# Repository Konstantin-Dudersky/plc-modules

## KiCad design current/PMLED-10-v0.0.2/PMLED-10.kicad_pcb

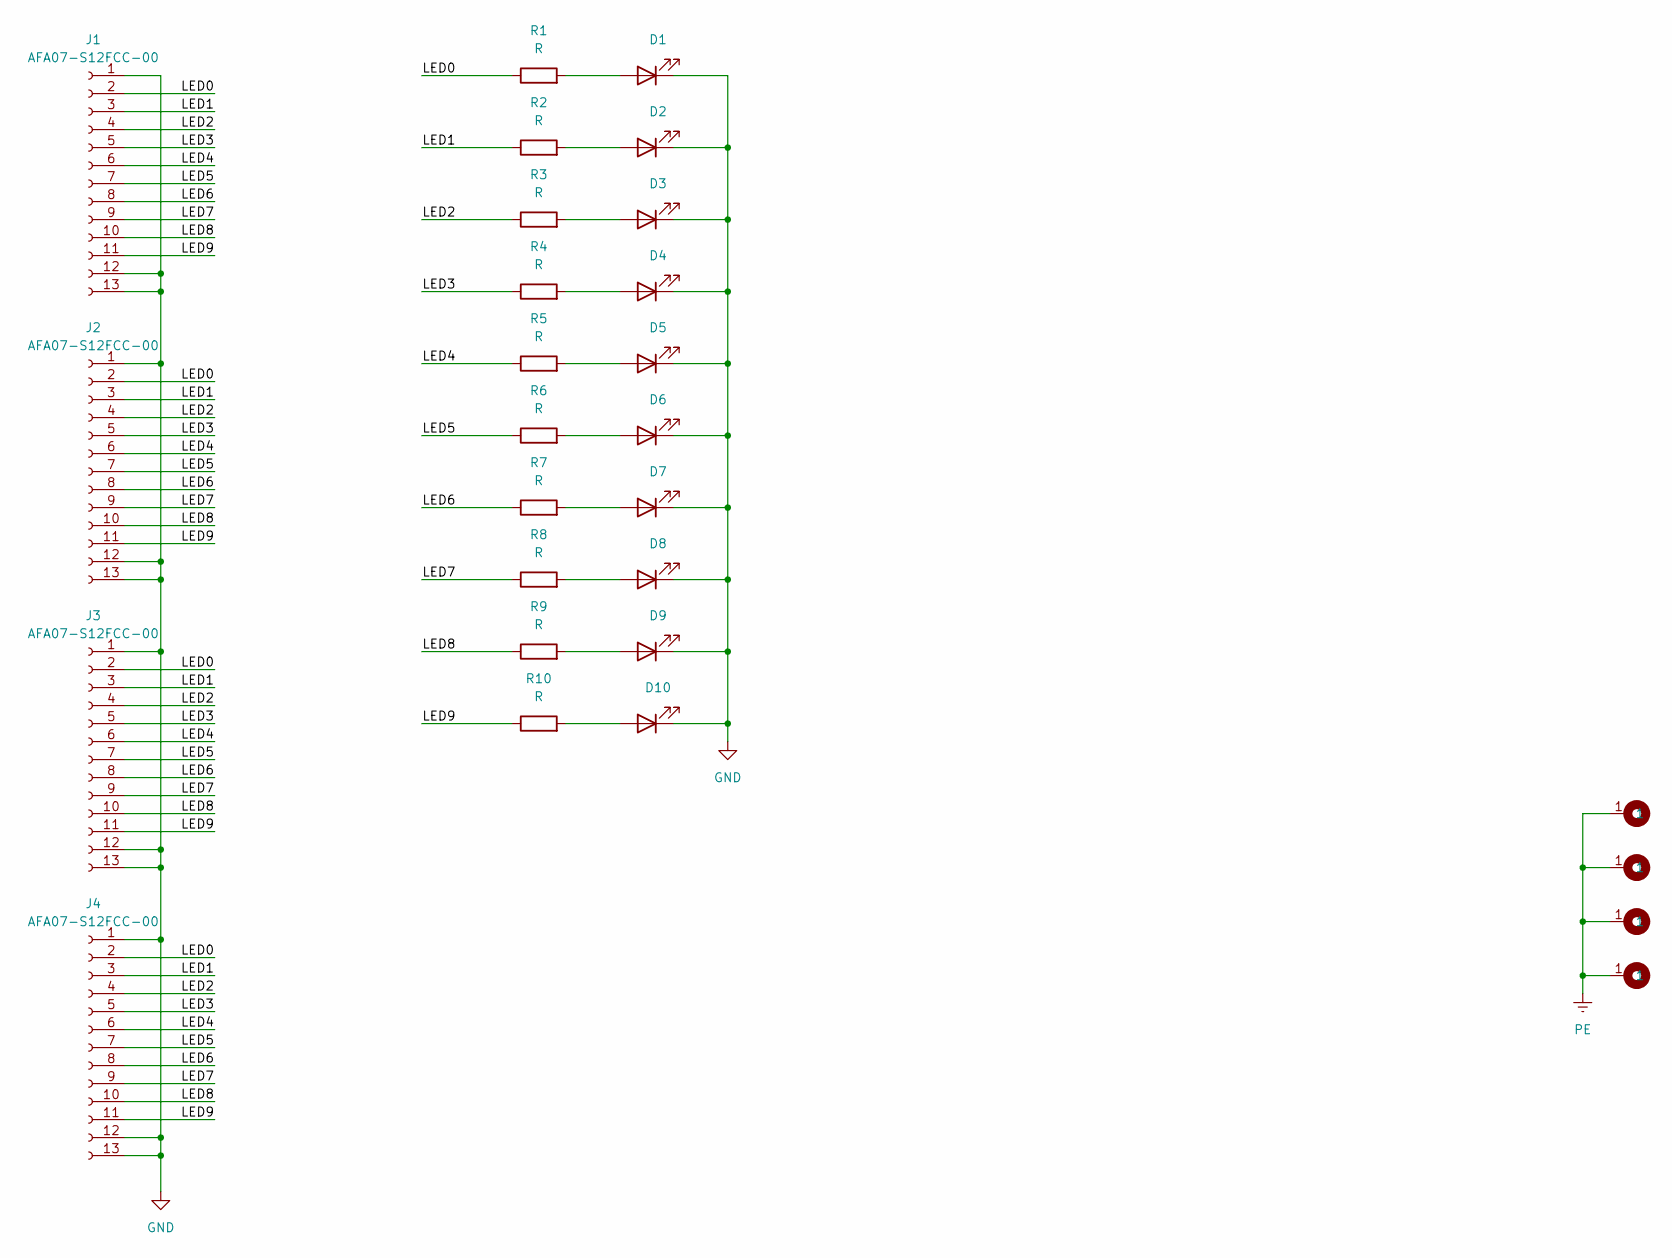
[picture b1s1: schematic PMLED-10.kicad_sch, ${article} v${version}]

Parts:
D1, D2, D3, D4, D5, D6, D7, D8, D9, D10: XL-1606SYGC; XL-1606; part_ipn XL-1606SYGC
H1, H2, H3, H5: M4; MountingHole_2.2mm_M2_Pad
J1, J2, J3, J4: AFA07-S12FCC-00; CONN10_AFA07-S12_JUS; part_ipn AFA07-S12FCC-00
R1, R2, R3, R4, R5, R6, R7, R8, R9, R10: R; R_0603_1608Metric

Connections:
/LED0: J1.2, J2.2, J3.2, J4.2, R1.1
/LED1: J1.3, J2.3, J3.3, J4.3, R2.1
/LED2: J1.4, J2.4, J3.4, J4.4, R3.1
/LED3: J1.5, J2.5, J3.5, J4.5, R4.1
/LED4: J1.6, J2.6, J3.6, J4.6, R5.1
/LED5: J1.7, J2.7, J3.7, J4.7, R6.1
/LED6: J1.8, J2.8, J3.8, J4.8, R7.1
/LED7: J1.9, J2.9, J3.9, J4.9, R8.1
/LED8: J1.10, J2.10, J3.10, J4.10, R9.1
/LED9: J1.11, J2.11, J3.11, J4.11, R10.1
GND: D1.1 (K), D2.1 (K), D3.1 (K), D4.1 (K), D5.1 (K), D6.1 (K), D7.1 (K), D8.1 (K), D9.1 (K), D10.1 (K), J1.1, J1.12 (Pin_11), J1.13 (Pin_11), J2.1, J2.12 (Pin_11), J2.13 (Pin_11), J3.1, J3.12 (Pin_11), J3.13 (Pin_11), J4.1, J4.12 (Pin_11), J4.13 (Pin_11)
unnamed: D1.2 (A), R1.2
unnamed: D2.2 (A), R2.2
unnamed: D3.2 (A), R3.2
unnamed: D4.2 (A), R4.2
unnamed: D5.2 (A), R5.2
unnamed: D6.2 (A), R6.2
unnamed: D7.2 (A), R7.2
unnamed: D8.2 (A), R8.2
unnamed: D9.2 (A), R9.2
unnamed: D10.2 (A), R10.2
PE: H1.1, H2.1, H3.1, H5.1

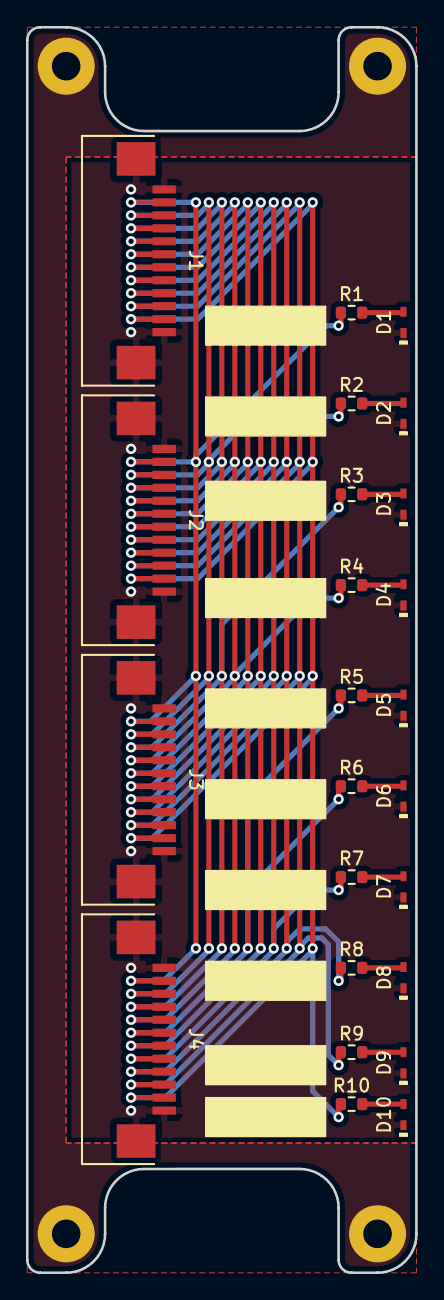
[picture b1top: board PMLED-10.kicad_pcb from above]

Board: 2 copper layers, 30.0 x 96.0 mm, 29 parts (1 on the bottom side), 22 nets.

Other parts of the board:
Logo_kicad: KiCad-Logo2_5mm_SilkScreen

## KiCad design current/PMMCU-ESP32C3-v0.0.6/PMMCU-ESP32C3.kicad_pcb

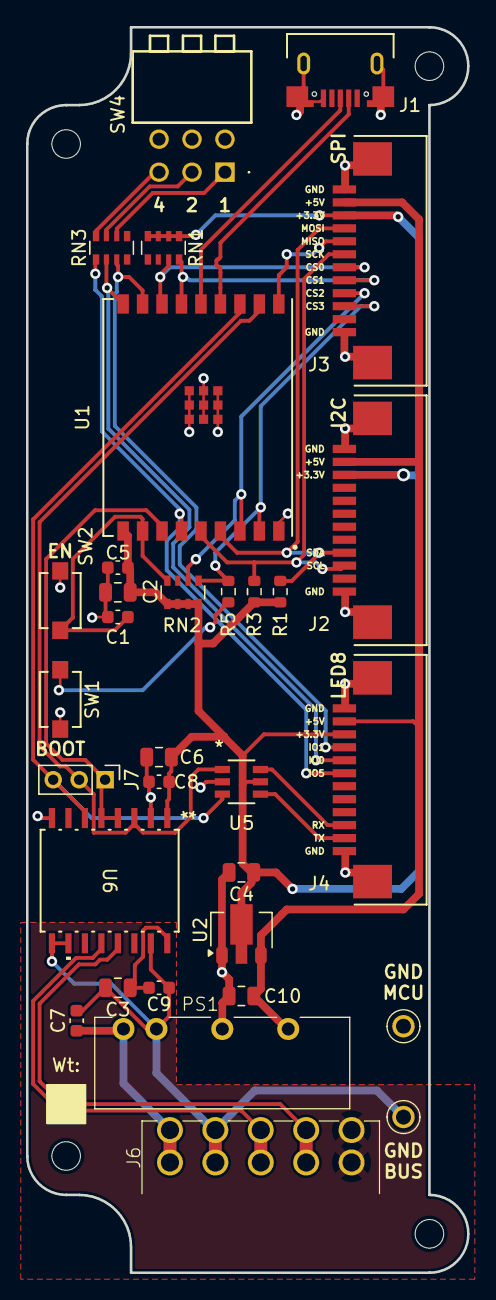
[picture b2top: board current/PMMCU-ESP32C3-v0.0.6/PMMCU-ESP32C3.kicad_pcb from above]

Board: 2 copper layers, 34.0 x 96.0 mm, 36 parts (0 on the bottom side), 31 nets.

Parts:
C1, C5, C7: 1uF; C_0603_1608Metric
C2, C3, C6, C10: 10uF; C_0805_2012Metric
C4: 22uF; C_0805_2012Metric
C8, C9: 100nF; C_0603_1608Metric
H1, H2, H3, H4: MountingHole_M2
J1: U254-051T-4BH83-S1S; CONN5_H83-S1S_XKB
J2, J3, J4: AFA07-S12FCC-00; CONN10_AFA07-S12_JUS
J6: 15EDGRHC-THR-3.5-10P
J7: PinHeader_01x03_P2.00_THT_straight; PinHeader_1x03_P2.00mm_Vertical
PS1: 24V/5V; B2405LS-1WR3
R1, R3: 3k3; R_0603_1608Metric
R5: 330R; R_0603_1608Metric
RN1, RN2, RN3: 10k; R_Array_Convex_4x0603
SW1, SW2: Button; SW_TS-1088_XNP-M
SW4: DIP 3 pos; DA03BLP
U1: ESP32-C3-WROOM-02U-N4; ESP32-C3-WROOM-02U_EXP
U2: CJA1117B-3.3; SOT-89-3
U3, U4: 5117
U5: SN74LVC2G14DBVR; DBV6-M
U6: CA-IS3098W; SOIC16-WBW_CLG

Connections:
+3.3V_BUS: C3.1, C9.1, U6.16 (VISO)
+3.3V_MCU: C2.1, C4.1, C5.1, C6.1, C8.1, J2.10, J3.10, J4.10, R1.1, R3.1, RN1.1 (R1.1), RN1.2 (R2.1), RN1.3 (R3.1), RN1.4 (R4.1), RN2.1 (R1.1), RN2.2 (R2.1), RN2.3 (R3.1), RN2.4 (R4.1), U1.1 (3V3), U2.2 (OUTPUT), U5.5 (VCC), U6.1 (VDD)
+5V_MCU: C10.1, J2.11, J3.11, J4.11, PS1.6 (+V), U2.3 (INPUT)
+24V_BUS: C7.1, J6.1, J6.6 (Pin_2), PS1.1 (Vin)
/A: J6.3, J6.8 (Pin_6), U6.12 (A)
/B: J6.4, J6.9 (Pin_8), U6.13 (B)
/CS0: J3.6, RN1.7 (R2.2), U1.16 (IO2)
/CS1: J3.5, RN1.8 (R1.2), U1.15 (IO3)
/CS2: J3.4, RN2.6 (R3.2), U1.7 (IO8)
/CS3: J3.3, R5.2, RN2.5 (R4.2), U1.8 (IO9)
/EN: C1.1, RN2.8 (R1.2), SW2.2, U1.2 (EN)
/LED0: J4.9, RN3.7 (R2.2), U1.17 (IO1)
/LED1: J4.8, RN3.6 (R3.2), U1.18 (IO0)
/LED2: J4.7, RN3.5 (R4.2), U1.4 (IO5)
/MISO: J3.8, U1.10 (IO10)
/MOSI: J2.4, J3.9, R1.2, U1.6 (IO7)
/SCK: J2.3, J3.7, R3.2, U1.5 (IO6)
/UART_RTS: J7.1, U1.3 (IO4), U6.4 (RE), U6.5 (DE)
/UART_RX: J7.2, U1.11 (RXD_(IO20)), U5.1 (1A), U6.3 (RO)
/UART_TX: J7.3, U1.12 (TXD_(IO21)), U5.3 (2A), U6.6 (DI)
/USB_D+: J1.3 (D+), U1.14 (IO19_(USB_D+))
/USB_D-: J1.2 (D-), U1.13 (IO18_(USB_D-))
GND_BUS: C3.2, C7.2, C9.2, J6.2 (Pin_3), J6.7 (Pin_4), PS1.2 (GND), U4.1, U6.9 (GNDB), U6.10 (SEL), U6.15 (GNDB)
GND_MCU: C1.2, C2.2, C4.2, C5.2, C6.2, C8.2, C10.2, J1.5 (GND), J2.1, J2.12 (Pin_11), J2.13 (Pin_11), J3.1, J3.12 (Pin_11), J3.13 (Pin_11), J4.1, J4.12 (Pin_11), J4.13 (Pin_11), PS1.4 (0V), SW1.1, SW2.1, SW4.4, SW4.5, SW4.6, U1.9 (GND), U1.EPAD, U2.1 (GND), U3.1, U5.2 (GND), U6.2 (GNDA), U6.8 (GNDA)
unnamed: J4.2, U5.4 (2Y)
unnamed: J4.3, U5.6 (1Y)
unnamed: R5.1, SW1.2
unnamed: RN3.2 (R2.1), SW4.1
unnamed: RN3.3 (R3.1), SW4.2
unnamed: RN3.4 (R4.1), SW4.3
PE: J6.5 (Pin_9), J6.10

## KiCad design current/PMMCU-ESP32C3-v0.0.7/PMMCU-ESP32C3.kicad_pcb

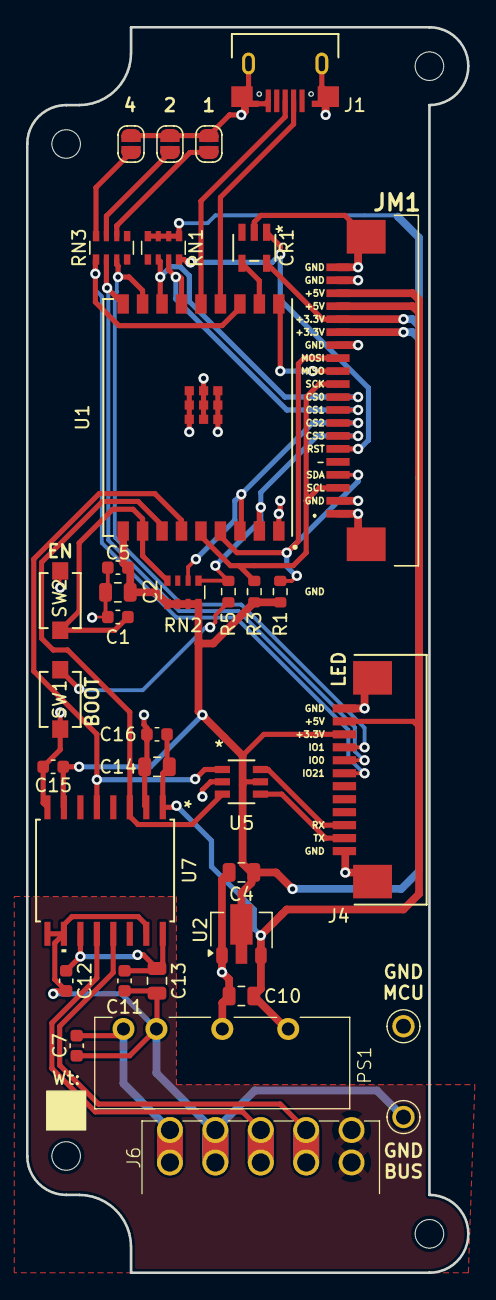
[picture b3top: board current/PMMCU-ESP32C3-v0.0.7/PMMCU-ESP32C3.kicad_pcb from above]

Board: 2 copper layers, 34.0 x 96.0 mm, 39 parts (0 on the bottom side), 32 nets.

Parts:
C1, C5, C7, C12, C15: 1uF; C_0603_1608Metric
C2, C10, C13, C14: 10uF; C_0805_2012Metric
C4: 22uF; C_0805_2012Metric
C11, C16: 100nF; C_0603_1608Metric
CR1: STWD100NYWY3F; SOT23-5L_STM
H1, H2, H3, H4: MountingHole_M2
J1: U254-051T-4BH83-S1S; CONN5_H83-S1S_XKB
J4: AFA07-S12FCC-00; CONN10_AFA07-S12_JUS
J6: 15EDGRHC-THR-3.5-10P
JM1: AFA07-S20FCC-00; AFA07S20FCA00
JP1, JP2, JP3: SolderJumper_2_Open; SolderJumper-2_P1.3mm_Open_RoundedPad1.0x1.5mm
PS1: 24V/5V; B2405LS-1WR3
R1, R3: 3k3; R_0603_1608Metric
R5: 330R; R_0603_1608Metric
RN1, RN2, RN3: 10k; R_Array_Convex_4x0603
SW1, SW2: Button; SW_TS-1088_XNP-M
U1: ESP32-C3-WROOM-02U-N4; ESP32-C3-WROOM-02U_EXP
U2: CJA1117B-3.3; SOT-89-3
U3, U4: 5117
U5: SN74LVC2G14DBVR; DBV6-M
U7: CA-IS3062VW; SOIC16-WBW_CLG-M

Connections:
+3.3V_MCU: C2.1, C4.1, C5.1, C15.1, CR1.5 (VCC), J4.10, JM1.15 (Pin_11), JM1.16 (Pin_11), R1.1, R3.1, RN1.1 (R1.1), RN1.2 (R2.1), RN1.3 (R3.1), RN1.4 (R4.1), RN2.1 (R1.1), RN2.2 (R2.1), RN2.3 (R3.1), RN2.4 (R4.1), U1.1 (3V3), U2.2 (OUTPUT), U5.5 (VCC), U7.7 (Vccl)
+5V_BUS: C11.1, C12.1, C13.1, U7.11 (Visoin), U7.16 (Viso)
+5V_MCU: C10.1, C14.1, C16.1, J4.11, JM1.17 (Pin_11), JM1.18 (Pin_11), PS1.6 (+V), U2.3 (INPUT), U7.1 (Vcc)
+24V_BUS: C7.1, J6.1, J6.6 (Pin_2), PS1.1 (Vin)
/CANH_BUS: J6.4, J6.9 (Pin_8), U7.13 (CANH)
/CANL_BUS: J6.3, J6.8 (Pin_6), U7.12 (CANL)
/CAN_RX: U1.4 (IO5), U5.1 (1A), U7.5 (RXD)
/CAN_TX: U1.3 (IO4), U5.3 (2A), U7.3 (TXD)
/CS0_MCU: JM1.10, RN1.6 (R3.2), U1.16 (IO2)
/CS1_MCU: JM1.9, RN1.7 (R2.2), U1.15 (IO3)
/CS2_MCU: JM1.8, RN2.6 (R3.2), U1.7 (IO8)
/CS3_MCU: JM1.7, R5.2, RN2.5 (R4.2), U1.8 (IO9)
/EN: C1.1, RN2.8 (R1.2), SW2.2, U1.2 (EN)
/LED0: J4.9, RN3.7 (R2.2), U1.17 (IO1)
/LED1: J4.8, RN3.6 (R3.2), U1.18 (IO0)
/LED2: J4.7, RN3.5 (R4.2), U1.12 (TXD_(IO21))
/MISO_MCU: JM1.12 (Pin_11), U1.10 (IO10)
/MOSI_SDA_MCU: JM1.4, JM1.13 (Pin_11), R1.2, U1.6 (IO7)
/RST: CR1.1 (*WDO), JM1.6, RN1.8 (R1.2)
/SCK_SCL_MCU: JM1.3, JM1.11, R3.2, U1.5 (IO6)
/USB_D+: J1.3 (D+), U1.14 (IO19_(USB_D+))
/USB_D-: J1.2 (D-), U1.13 (IO18_(USB_D-))
/WDT: CR1.4 (WDI), U1.11 (RXD_(IO20))
GND_BUS: C7.2, C11.2, C12.2, C13.2, J6.2 (Pin_3), J6.7 (Pin_4), PS1.2 (GND), U4.1, U7.9 (GND2), U7.10 (GND2), U7.15 (GND2)
GND_MCU: C1.2, C2.2, C4.2, C5.2, C10.2, C14.2, C15.2, C16.2, CR1.2 (GND), J1.5 (GND), J4.1, J4.12 (Pin_11), J4.13 (Pin_11), JM1.1, JM1.2, JM1.14 (Pin_11), JM1.19 (Pin_11), JM1.20 (Pin_11), JM1.MP1 (Pin_11), JM1.MP2 (Pin_11), JP1.2 (B), JP2.2 (B), JP3.2 (B), PS1.4 (0V), SW1.1, SW2.1, U1.9 (GND), U1.EPAD, U2.1 (GND), U3.1, U5.2 (GND), U7.2 (GND1), U7.8 (GND1)
unnamed: J4.2, U5.4 (2Y)
unnamed: J4.3, U5.6 (1Y)
unnamed: JP1.1 (A), RN3.4 (R4.1)
unnamed: JP2.1 (A), RN3.3 (R3.1)
unnamed: JP3.1 (A), RN3.2 (R2.1)
unnamed: R5.1, SW1.2
PE: J6.5 (Pin_9), J6.10

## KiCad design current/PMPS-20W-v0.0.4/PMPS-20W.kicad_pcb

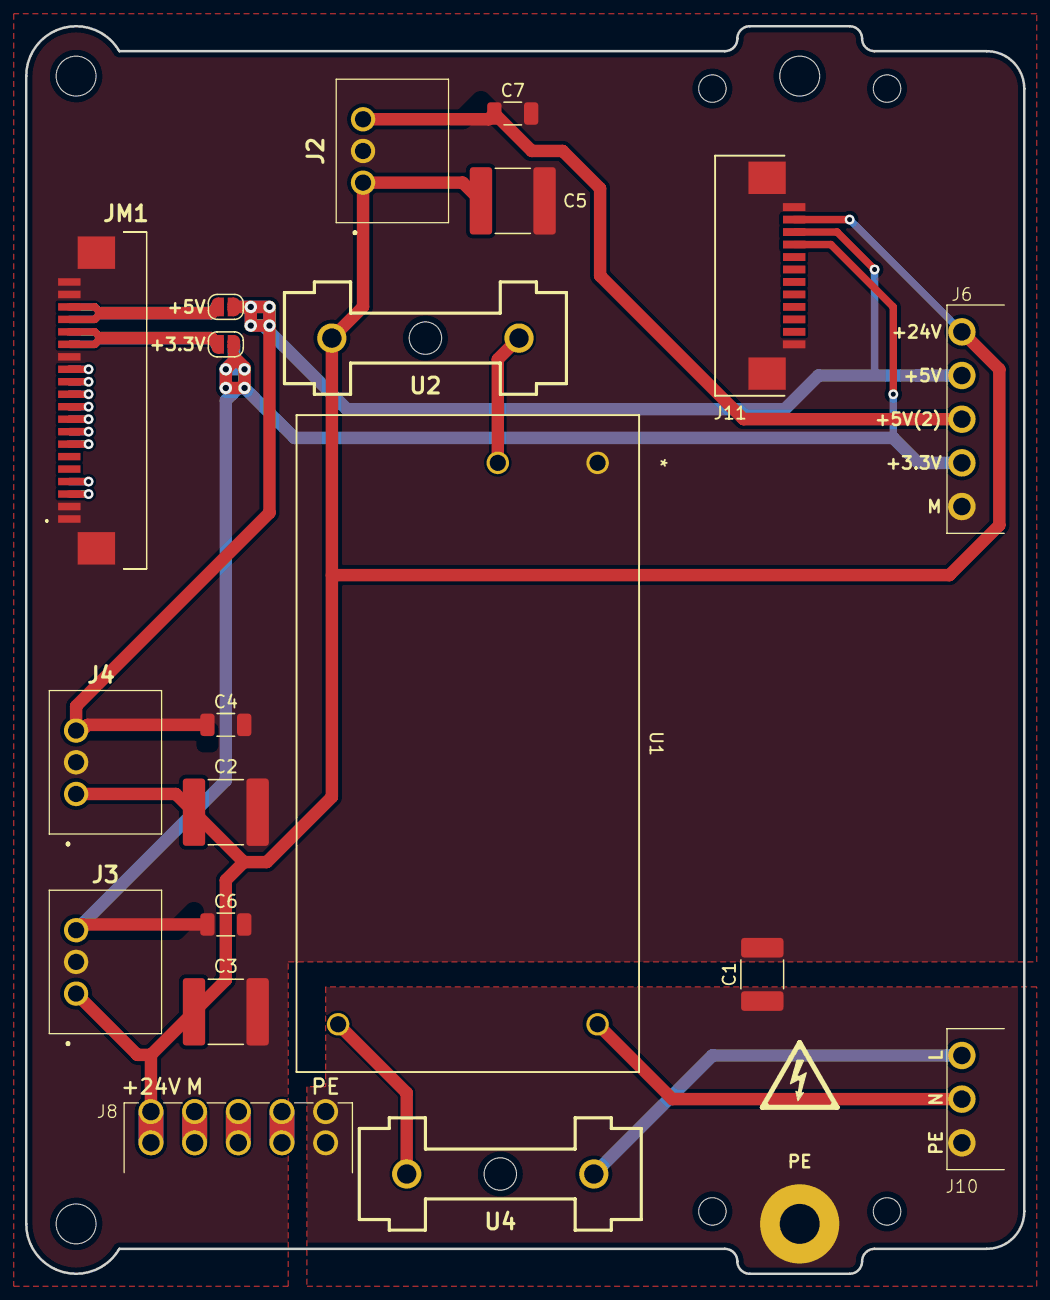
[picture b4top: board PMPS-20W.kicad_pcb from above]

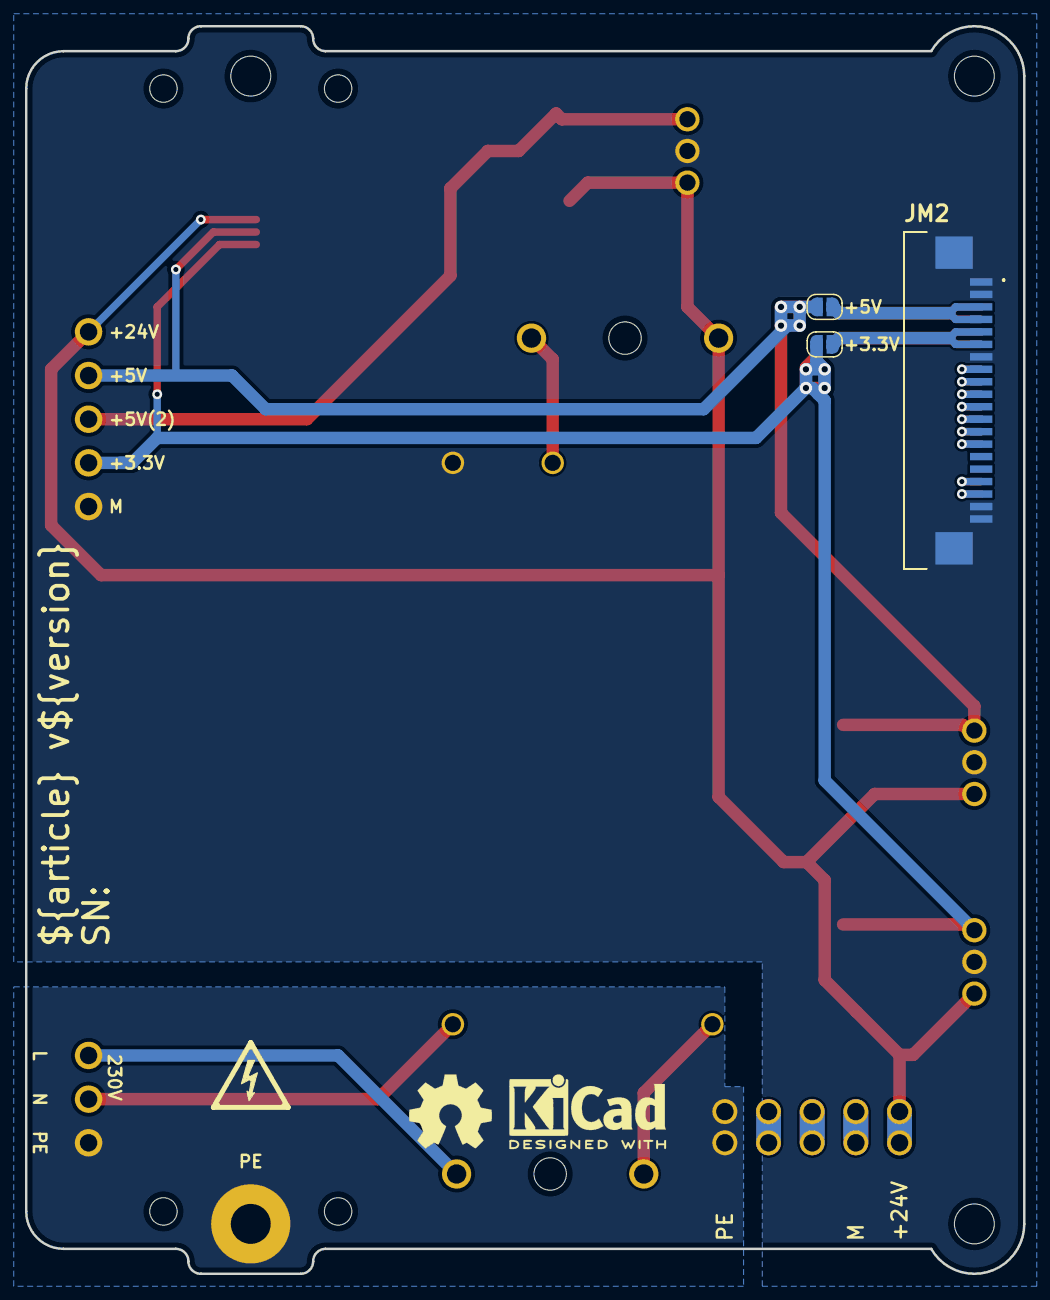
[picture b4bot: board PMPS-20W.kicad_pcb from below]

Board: 2 copper layers, 80.0 x 100.0 mm, 30 parts (5 on the bottom side), 29 nets.

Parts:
C1: 4.7nF 2kV; C_1812_4532Metric_Pad1.57x3.40mm_HandSolder
C2, C3, C5: 22uF; C_2220_5750Metric
C4, C6, C7: 22uF; C_1206_3216Metric
H1, H2, H3: MountingHole_M3
J2, J4: K7805-2000R3
J3: K7803-2000R3; K7805-2000R3
J6: 15EDGRC-3.5-05P
J8: 15EDGRHC-THR-3.5-10P
J10: 15EDGRC-3.5-03P
J11: AFA07-S12FCC-00; CONN10_AFA07-S12_JUS
JM1, JM2: AFA07-S20FCC-00; AFA07S20FCA00
JP1, JP2, JP3, JP4: SolderJumper_2_Open; SolderJumper-2_P1.3mm_Open_RoundedPad1.0x1.5mm
PE1: PE
SP1: PM_LED-xx-v0.0.1
U1: IRM-20-24; IRM-20-24_MWU
U2, U4: 64900001039; 649-Series-Holder
kicad_logo: KiCad-Logo2_5mm_SilkScreen
oshw_logo: OSHW-Symbol_6.7x6mm_SilkScreen

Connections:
230V: J10.3, U4.1
+3V3: C6.1, J3.3 (+VO), J6.2, J11.4, JP3.2 (B), JP4.1 (A)
+3V3-IB-back: JM2.5, JM2.6, JP4.2 (B)
+3V3-IB-front: JM1.15 (Pin_11), JM1.16 (Pin_11), JP3.1 (A)
+5V: C4.1, J4.3 (+VO), J6.4, J11.3, JP1.2 (B), JP2.1 (A)
+5V(2): C7.1, J2.3 (+VO), J6.3
+5V-IB-back: JM2.3, JM2.4, JP2.2 (B)
+5V-IB-front: JM1.17 (Pin_11), JM1.18 (Pin_11), JP1.1 (A)
+24V: C2.1, C3.1, C5.1, J2.1 (VIN), J3.1 (VIN), J4.1 (VIN), J6.5, J11.2, U2.2
+24V_EB: J8.1, J8.6 (Pin_2)
/CANH_EB: J8.4, J8.9 (Pin_8)
/CANL_EB: J8.3, J8.8 (Pin_6)
/CS0_IB: JM1.10, JM2.11
/CS1_IB: JM1.9, JM2.12 (Pin_11)
/CS2_IB: JM1.8, JM2.13 (Pin_11)
/CS3_IB: JM1.7, JM2.14 (Pin_11)
/MISO_IB: JM1.12 (Pin_11), JM2.9
/MOSI_IB: JM1.13 (Pin_11), JM2.8
/RST_IB: JM1.6, JM2.15 (Pin_11)
/SCK_IB: JM1.11, JM2.10
/SCL_IB: JM1.3, JM2.18 (Pin_11)
/SDA_IB: JM1.4, JM2.17 (Pin_11)
GND_EB: J8.2 (Pin_3), J8.7 (Pin_4)
GND_MCU: C1.2, C2.2, C3.2, C4.2, C5.2, C6.2, C7.2, J2.2 (GND), J3.2 (GND), J4.2 (GND), J6.1, J11.1, J11.12 (Pin_11), J11.13 (Pin_11), JM1.1, JM1.2, JM1.14 (Pin_11), JM1.19 (Pin_11), JM1.20 (Pin_11), JM1.MP1 (Pin_11), JM1.MP2 (Pin_11), JM2.1, JM2.2, JM2.7, JM2.19 (Pin_11), JM2.20 (Pin_11), JM2.MP1 (Pin_11), JM2.MP2 (Pin_11), U1.1 (V-)
N: J10.2, U1.4 (AC/N)
unnamed: JM1.5, JM2.16 (Pin_11)
unnamed: U1.3 (AC/L), U4.2
unnamed: U1.2 (V+), U2.1
PE: C1.1, J8.5 (Pin_9), J8.10, J10.1, PE1.1

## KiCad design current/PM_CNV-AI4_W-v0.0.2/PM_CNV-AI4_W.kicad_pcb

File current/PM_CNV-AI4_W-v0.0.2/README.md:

## v0.0.2

- Вместо двух AD7190 - один AD7193

Подключить GND к AINCOM

Подключить референс только к Refin1

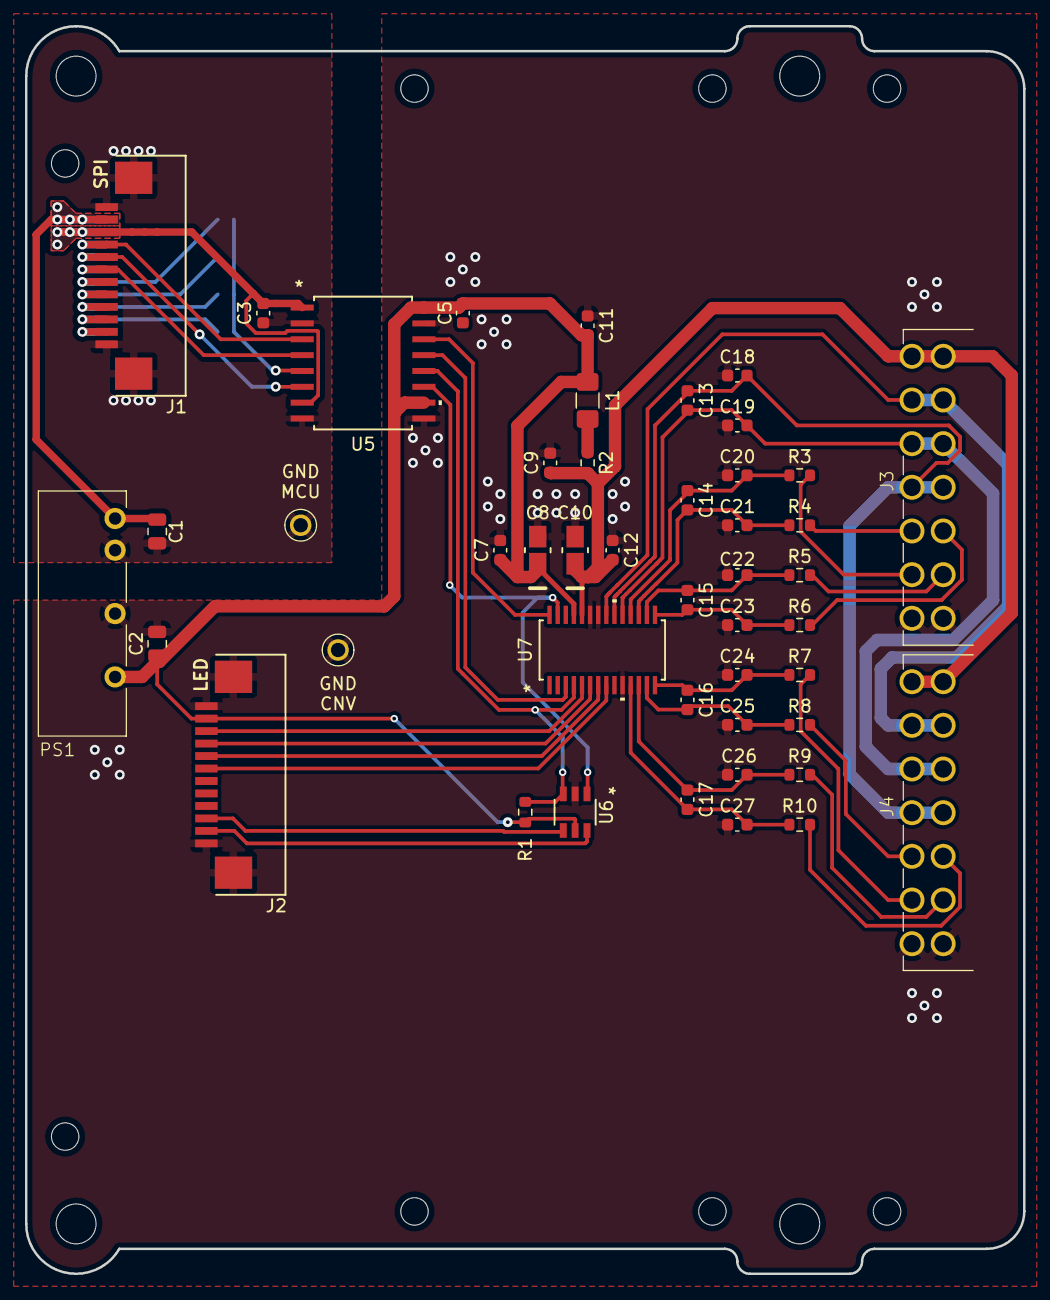
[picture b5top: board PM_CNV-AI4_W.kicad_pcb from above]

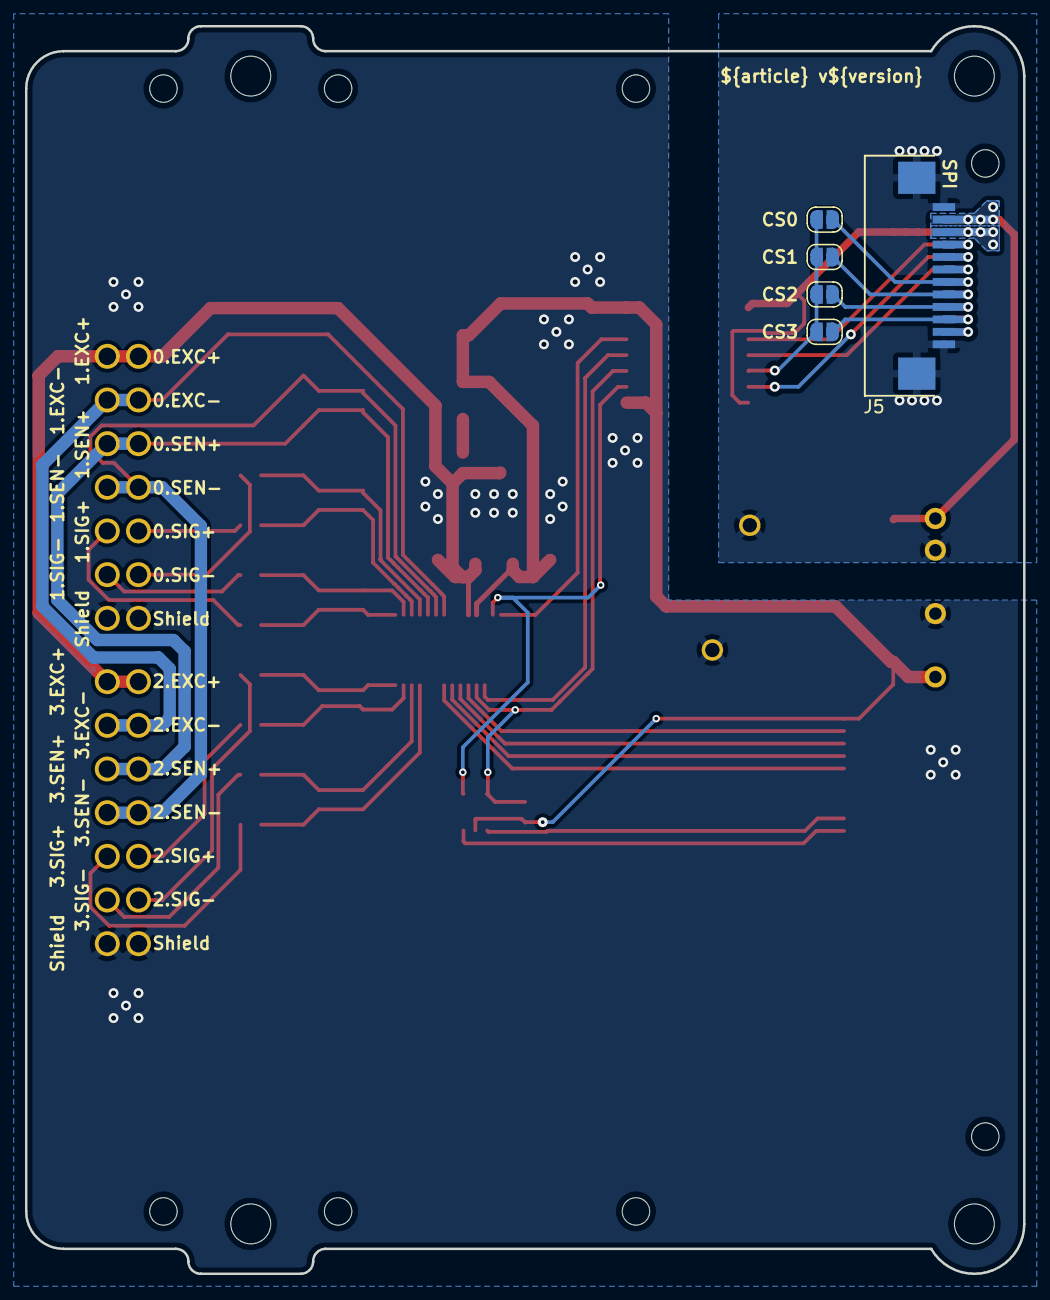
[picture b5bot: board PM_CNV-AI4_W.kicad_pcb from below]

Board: 2 copper layers, 80.0 x 100.0 mm, 57 parts (5 on the bottom side), 45 nets.

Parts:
C1: 4.7uF; C_0805_2012Metric
C2: 10uF; C_0805_2012Metric
C3, C5, C7, C9, C11, C12: 100nF; C_0603_1608Metric
C8, C10: 10 uF; TAJA_AVX-M
C13: 1uF; C_0603_1608Metric
C14, C15, C16, C17, C18, C19: 10nF; C_0603_1608Metric
C20, C21, C22, C23, C24, C25, C26, C27: 1nF; C_0603_1608Metric
H1, H2, H3, H4: MountingHole_M3
J1, J2, J5: AFA07-S12FCC-00; CONN10_AFA07-S12_JUS
J3, J4: 15EDGRHC-THR-3.5-14P
JP1, JP2, JP3, JP4: SolderJumper_2_Open; SolderJumper-2_P1.3mm_Open_RoundedPad1.0x1.5mm
L1: 1kΩ@100MHz; L_1206_3216Metric_Pad1.42x1.75mm_HandSolder
PS1: 5V/5V; B2405LS-1WR3
R1: 10k; R_0603_1608Metric
R2: 1R5; R_0603_1608Metric
R3, R4, R5, R6, R7, R8, R9, R10: 100R; R_0603_1608Metric
SP1: PM_LED-xx-v0.0.1
U1: PM-ESP32C3_v0.0.5
U2, U3: 5117
U5: CA-IS3741HW; SOIC16-WBW_CLG-M
U6: SN74LVC2G14DBVR; DBV6-M
U7: AD7193BRUZ; RU_28_ADI

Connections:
+3.3V_MCU: C3.1, J1.10, J5.3, U5.1 (VDD), U5.7 (ENA)
+5V_CNV: C2.1, C5.2, C7.1, C8.1, C11.1, J2.11, L1.2, PS1.6 (+V), R1.1, U5.10 (ENB), U5.16 (VISO), U6.5 (VCC), U7.25 (DVDD)
+5V_CNV_FLT: C9.1, C10.1, C12.1, J3.7 (Pin_9), J3.14 (Pin_10), J4.7 (Pin_9), J4.14 (Pin_10), R2.2, U7.24 (AVDD)
+5V_MCU: C1.1, J1.11, J5.2, PS1.1 (Vin)
/0.SIG+: J3.3, R4.2
/0.SIG-: J3.2 (Pin_3), R3.2
/1.SIG+: J3.10 (Pin_6), R6.2
/1.SIG-: J3.9 (Pin_4), R5.2
/2.SIG+: J4.3, R8.2
/2.SIG-: J4.2 (Pin_3), R7.2
/3.SIG+: J4.10 (Pin_6), R10.2
/3.SIG-: J4.9 (Pin_4), R9.2
/AIN1: C17.1, C27.1, R10.1, U7.11 (AIN1)
/AIN2: C17.2, C26.1, R9.1, U7.12 (AIN2)
/AIN3: C16.1, C25.1, R8.1, U7.13 (AIN3)
/AIN4: C16.2, C24.1, R7.1, U7.14 (AIN4)
/AIN5: C15.1, C23.1, R6.1, U7.15 (AIN5)
/AIN6: C15.2, C22.1, R5.1, U7.16 (AIN6)
/AIN7: C14.1, C21.1, R4.1, U7.17 (AIN7)
/AIN8: C14.2, C20.1, R3.1, U7.18 (AIN8)
/CS0_MCU: J1.6, J5.7, JP1.1 (A)
/CS1_MCU: J1.5, J5.8, JP2.1 (A)
/CS2_MCU: J1.4, J5.9, JP3.1 (A)
/CS3_MCU: J1.3, J5.10, JP4.1 (A)
/CS_CNV: R1.2, U5.12 (VO3), U6.3 (2A), U7.4 (CS)
/CS_LED: J2.3, U6.4 (2Y)
/CS_MCU: JP1.2 (B), JP2.2 (B), JP3.2 (B), JP4.2 (B), U5.5 (VI3)
/EXC-: J3.6 (Pin_9), J3.13 (Pin_10), J4.6 (Pin_9), J4.13 (Pin_10), U7.21 (BPDSW)
/INT_MCU: J1.2, J5.11
/MISO_CNV: U5.11 (VI4), U6.1 (1A), U7.27 (MISO)
/MISO_LED: J2.2, U6.6 (1Y)
/MISO_MCU: J1.8, J5.5, U5.6 (VO4)
/MOSI_CNV: U5.14 (VO1), U7.28 (MOSI)
/MOSI_MCU: J1.9, J5.4, U5.3 (VI1)
/P0: J2.7, U7.8 (P0)
/P1: J2.8, U7.7 (P1)
/P2: J2.9, U7.6 (P2)
/P3: J2.10, U7.5 (P3)
/SCK_CNV: U5.13 (VO2), U7.3 (SCK)
/SCK_MCU: J1.7, J5.6, U5.4 (VI2)
/SENSE+: C13.1, C19.1, J3.5 (Pin_9), J3.12 (Pin_10), J4.5 (Pin_9), J4.12 (Pin_10), U7.19 (REFIN1(+))
/SENSE-: C13.2, C18.1, J3.4, J3.11 (Pin_8), J4.4, J4.11 (Pin_8), U7.20 (REFIN1(-))
GND_CNV: C2.2, C7.2, C8.2, C9.2, C10.2, C11.2, C12.2, C18.2, C19.2, C20.2, C21.2, C22.2, C23.2, C24.2, C25.2, C26.2, C27.2, J2.1, J2.12 (Pin_11), J2.13 (Pin_11), J3.1, J3.8 (Pin_2), J4.1, J4.8 (Pin_2), PS1.4 (0V), U3.1, U5.9 (GNDB), U5.15 (GNDB), U6.2 (GND), U7.10 (AINCOM), U7.22 (AGND), U7.23 (DGND)
GND_MCU: C1.2, C3.2, J1.1, J1.12 (Pin_11), J1.13 (Pin_11), J5.1, J5.12 (Pin_11), J5.13 (Pin_11), PS1.2 (GND), U2.1, U5.2 (GNDA), U5.8 (GNDA)
unnamed: L1.1, R2.1

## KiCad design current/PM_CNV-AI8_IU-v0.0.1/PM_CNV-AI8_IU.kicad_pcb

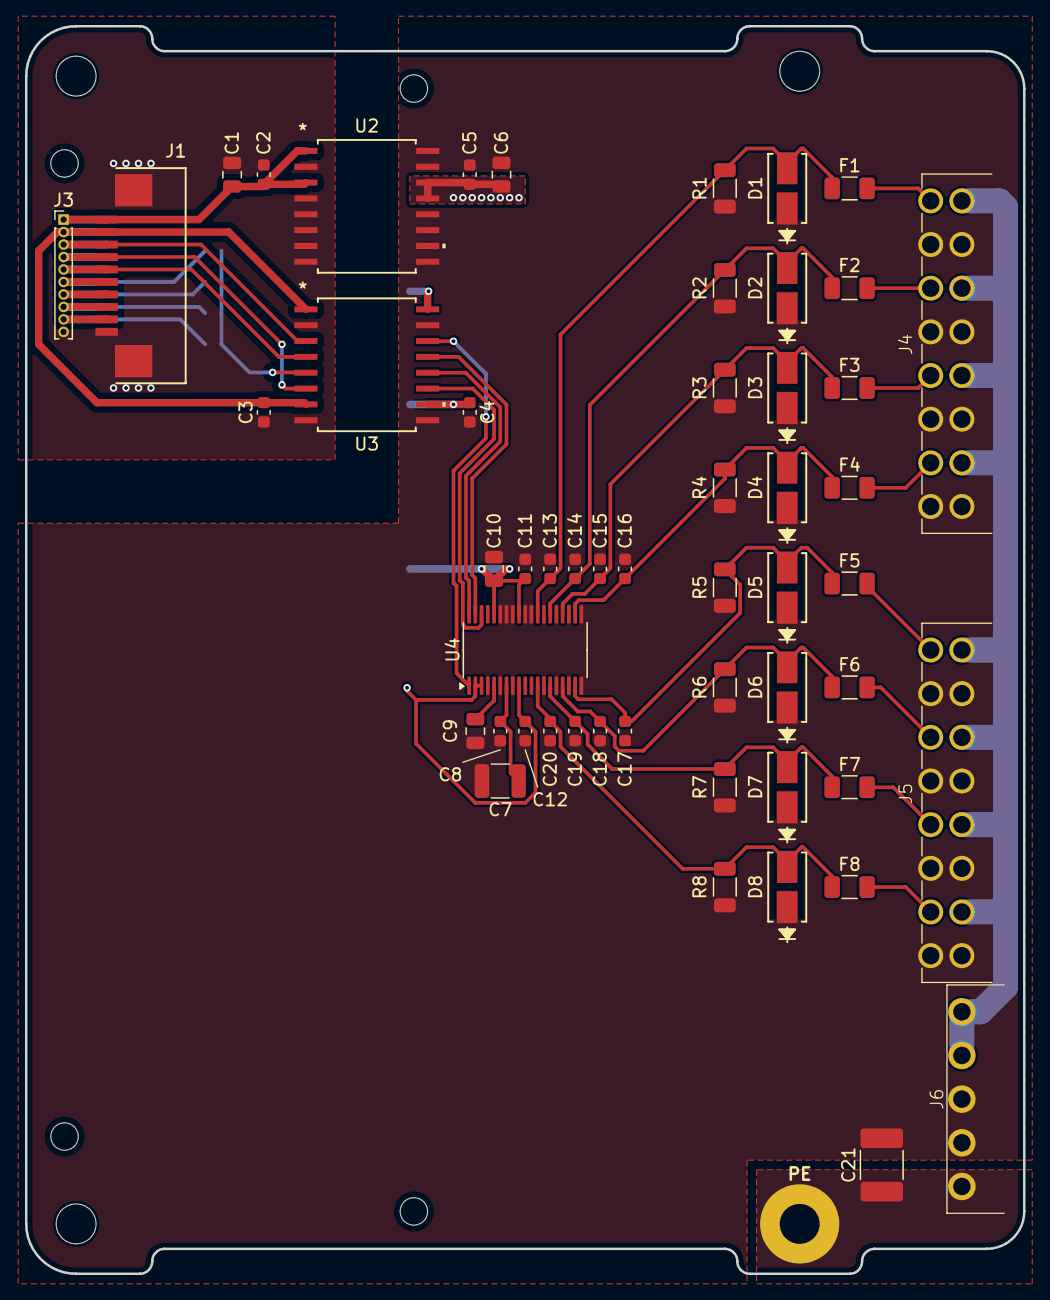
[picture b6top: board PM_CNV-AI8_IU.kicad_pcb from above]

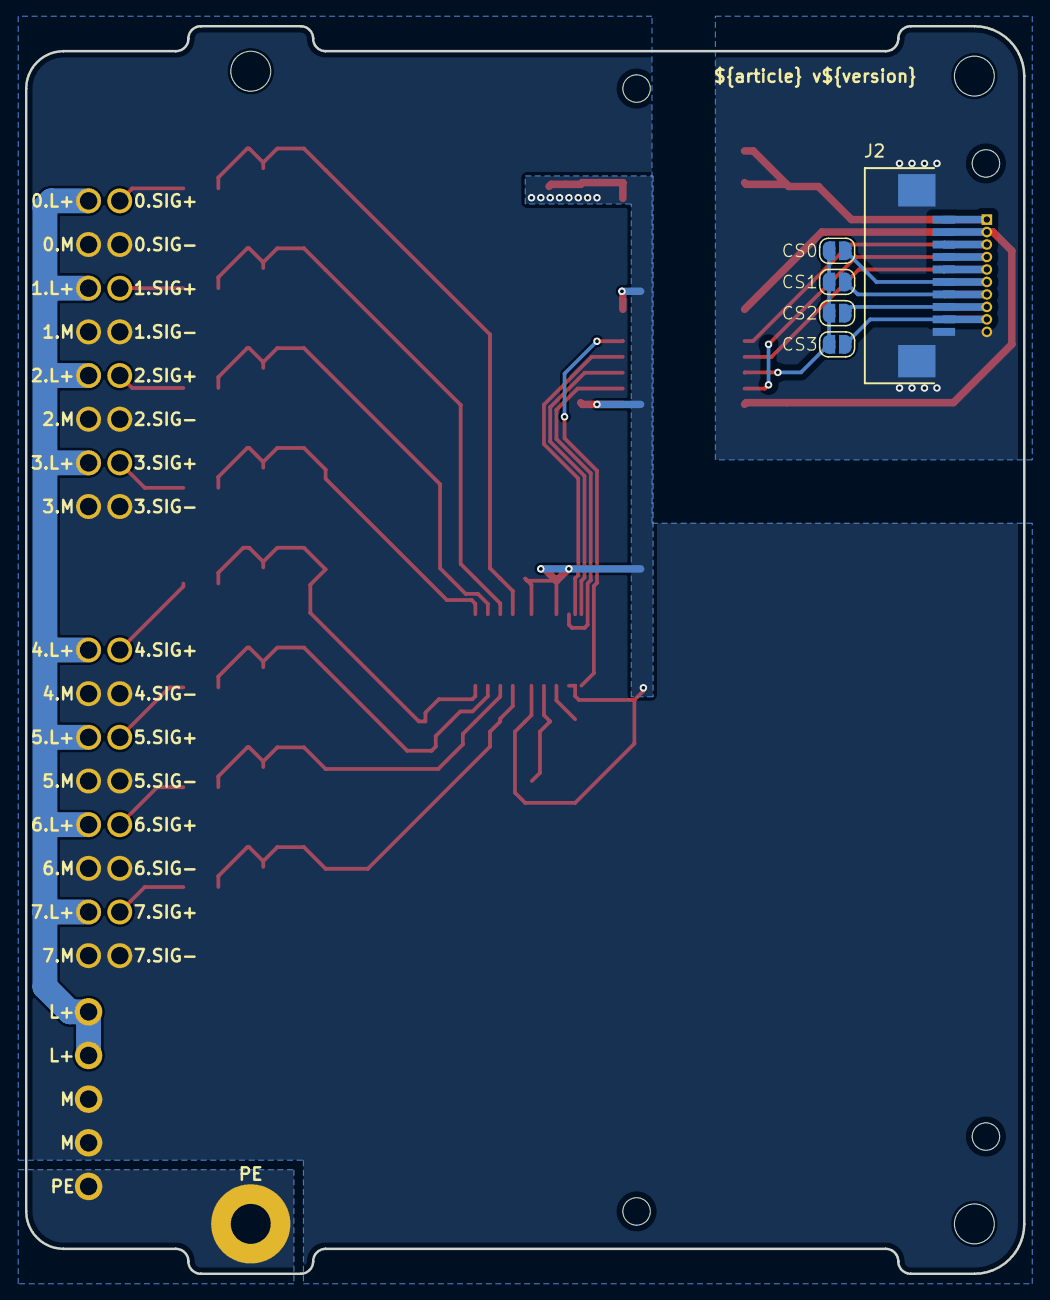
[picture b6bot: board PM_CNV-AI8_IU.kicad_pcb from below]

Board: 2 copper layers, 80.0 x 100.0 mm, 63 parts (5 on the bottom side), 37 nets.

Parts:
C1, C6, C9, C10: 10uF; C_0805_2012Metric
C2, C3, C4, C5: 100nF; C_0603_1608Metric
C7: 22uF; C_1210_3225Metric
C8, C11, C12: 1uF; C_0603_1608Metric
C13, C14, C15, C16, C17, C18, C19, C20: 10nF; C_0603_1608Metric
C21: 4.7nF 2kV; C_1812_4532Metric_Pad1.57x3.40mm_HandSolder
D1, D2, D3, D4, D5, D6, D7, D8: SMAJ33CA; SMASeries_LTF-M
D9: PE
F1, F2, F3, F4, F5, F6, F7, F8: nSMD005; Fuse_1206_3216Metric
H1, H2, H3: MountingHole; MountingHole_3.2mm_M3
J1, J2: AFA07-S10FCC-00; CONN10_AFA07-S10_JUS
J3: PinHeader_01x10_P1.00_THT_straight; PinHeader_1x10_P1.00mm_Vertical
J4, J5: 15EDGRHC-THR-3.5-16P
J6: 15EDGRC-3.5-05P
JP1, JP2, JP3, JP4: SolderJumper_2_Open; SolderJumper-2_P1.3mm_Open_RoundedPad1.0x1.5mm
R1, R2, R3, R4, R5, R6, R7, R8: 249R; R_1206_3216Metric
U1: PM-ESP32C3_v0.0.5
U2: CA-IS3105W; SOIC16-WBW_CLG-M
U3: CA-IS3741HW; SOIC16-WBW_CLG-M
U4: ADS8688; TSSOP-38_4.4x9.7mm_P0.5mm

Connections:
+3.3V_M: C3.2, J1.9, J2.2, J3.2, U3.1 (VDD), U3.7 (ENA)
+5V_F: C4.1, C5.1, C6.1, C10.2, C11.1, C12.1, U2.13 (SEL), U2.14 (VISO), U3.10 (ENB), U3.16 (VISO), U4.2 (~RST/PD), U4.3 (DAISY), U4.9 (AVDD), U4.30 (AVDD), U4.34 (DVDD)
+5V_M: C1.1, C2.1, J1.10, J2.1, J3.1, U2.1 (EN), U2.3 (VINP)
+24V_F: J4.10 (Pin_4), J4.12 (Pin_8), J4.14 (Pin_10), J4.16 (Pin_10), J5.10 (Pin_4), J5.12 (Pin_8), J5.14 (Pin_10), J5.16 (Pin_10), J6.4, J6.5
/0.SIG+: F1.2, J4.8 (Pin_9)
/1.SIG+: F2.2, J4.6 (Pin_9)
/2.SIG+: F3.2, J4.4
/3.SIG+: F4.2, J4.2 (Pin_3)
/4.SIG+: F5.2, J5.8 (Pin_9)
/5.SIG+: F6.2, J5.6 (Pin_9)
/6.SIG+: F7.2, J5.4
/7.SIG+: F8.2, J5.2 (Pin_3)
/AIN_0P: C18.1, D6.2 (A2), F6.1, R6.1, U4.16 (AIN_0P)
/AIN_1P: C17.1, D5.2 (A2), F5.1, R5.1, U4.18 (AIN_1P)
/AIN_2P: C16.1, D4.2 (A2), F4.1, R4.1, U4.21 (AIN_2P)
/AIN_3P: C15.1, D3.2 (A2), F3.1, R3.1, U4.23 (AIN_3P)
/AIN_4P: C14.1, D2.2 (A2), F2.1, R2.1, U4.25 (AIN_4P)
/AIN_5P: C13.1, D1.2 (A2), F1.1, R1.1, U4.27 (AIN_5P)
/AIN_6P: C20.1, D8.2 (A2), F8.1, R8.1, U4.12 (AIN_6P)
/AIN_7P: C19.1, D7.2 (A2), F7.1, R7.1, U4.14 (AIN_7P)
/CS0_M: J1.5, J2.6, J3.6, JP1.1 (A)
/CS1_M: J1.4, J2.7, J3.7, JP2.1 (A)
/CS2_M: J1.3, J2.8, J3.8, JP3.1 (A)
/CS3_M: J1.2, J2.9, J3.9, JP4.1 (A)
/CS_F: U3.12 (VO3), U4.38 (~CS)
/CS_M: JP1.2 (B), JP2.2 (B), JP3.2 (B), JP4.2 (B), U3.5 (VI3)
/MISO_F: U3.11 (VI4), U4.36 (SDO)
/MISO_M: J1.7, J2.4, J3.4, U3.6 (VO4)
/MOSI_F: U3.14 (VO1), U4.1 (SDI)
/MOSI_M: J1.8, J2.3, J3.3, U3.3 (VI1)
/SCK_F: U3.13 (VO2), U4.37 (SCLK)
/SCK_M: J1.6, J2.5, J3.5, U3.4 (VI2)
GND_F: C4.2, C5.2, C6.2, C7.2, C8.2, C9.2, C10.1, C11.2, C12.2, C13.2, C14.2, C15.2, C16.2, C17.2, C18.2, C19.2, C20.2, C21.2, D1.1 (A1), D2.1 (A1), D3.1 (A1), D4.1 (A1), D5.1 (A1), D6.1 (A1), D7.1 (A1), D8.1 (A1), J4.1, J4.3, J4.5 (Pin_9), J4.7 (Pin_9), J4.9 (Pin_2), J4.11 (Pin_6), J4.13 (Pin_10), J4.15 (Pin_10), J5.1, J5.3, J5.5 (Pin_9), J5.7 (Pin_9), J5.9 (Pin_2), J5.11 (Pin_6), J5.13 (Pin_10), J5.15 (Pin_10), J6.2, J6.3, R1.2, R2.2, R3.2, R4.2, R5.2, R6.2, R7.2, R8.2, U2.9 (GNDS), U2.10 (NC), U2.11 (NC), U2.12 (NC), U2.15 (GNDS), U2.16 (GNDS), U3.9 (GNDB), U3.15 (GNDB), U4.4 (~REFSEL), U4.6 (REFGND), U4.8 (AGND), U4.13 (AIN_6GND), U4.15 (AIN_7GND), U4.17 (AIN_0GND), U4.19 (AIN_1GND), U4.20 (AIN_2GND), U4.22 (AIN_3GND), U4.24 (AIN_4GND), U4.26 (AIN_5GND), U4.28 (AGND), U4.29 (AGND), U4.31 (AGND), U4.32 (AGND), U4.33 (DGND)
GND_M: C1.2, C2.2, C3.1, J1.1, J1.11, J2.10, J2.11, J3.10, U2.2 (GNDP), U2.4 (NC), U2.5 (NC), U2.6 (NC), U2.7 (NC), U2.8 (NC), U3.2 (GNDA), U3.8 (GNDA)
unnamed: C7.1, C8.1, U4.7 (REFCAP)
unnamed: C9.1, U4.5 (REFIO)
PE: C21.1, D9.1, J6.1
